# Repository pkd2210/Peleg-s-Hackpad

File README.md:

# Peleg's Hackpad

My HACKPAD version, it contains 5 button:
SW1 - toggle deafen (discord) - 1
SW 2 - toggle mute (discord) - 2
SW 3 - Stop / Start music - 4
SW 4 - next song - 3
SW 5 - Windows + l (sleep) - 0

My Schematic:

The PCB:

List of materials:
LED_SMD *2
SW_push * 5
XIAO-RP2040-DIP * 1

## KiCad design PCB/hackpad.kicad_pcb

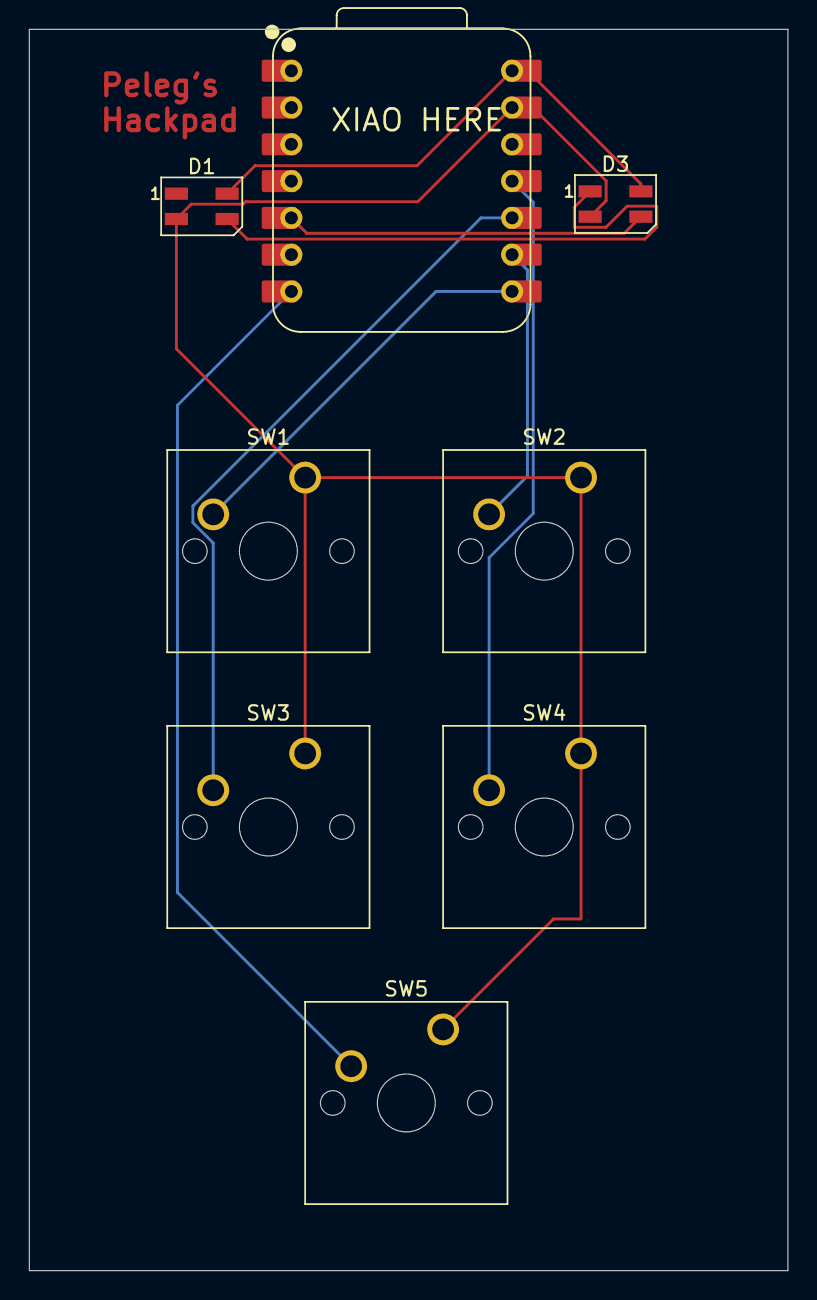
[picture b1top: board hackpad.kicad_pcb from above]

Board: 2 copper layers, 52.4 x 85.7 mm, 8 parts (0 on the bottom side), 8 nets.

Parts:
D1, D3: SK6812MINI; LED_SK6812MINI_PLCC4_3.5x3.5mm_P1.75mm
SW1, SW2, SW3, SW4, SW5: SW_Push; SW_Cherry_MX_1.00u_PCB
U1: XIAO-RP2040-DIP

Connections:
+5V: D1.4 (VDD), D3.4 (VDD), U1.14 (VBUS)
GND: D1.2 (VSS), D3.2 (VSS), SW1.1, SW2.1, SW3.1, SW4.1, SW5.1, U1.13 (GND)
unnamed: D1.3 (DIN), D3.1 (DOUT)
unnamed: D3.3 (DIN), U1.5 (GPIO6/SDA)
unnamed: SW1.2, U1.8 (GPIO1/RX)
unnamed: SW2.2, U1.9 (GPIO2/SCK)
unnamed: SW4.2, U1.11 (GPIO3/MOSI)
unnamed: SW3.2, U1.10 (GPIO4/MISO)

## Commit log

2025-07-28 Created the GIT PROJECT
2025-07-28 Updated README and added a pcb file
